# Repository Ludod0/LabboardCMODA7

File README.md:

# Cmod A7 — LabBoard V1

**A custom FPGA expansion PCB designed for the Digilent Cmod A7-35T.**

The **LabBoard V1** is a custom-designed PCB that expands the input/output capabilities of the Digilent Cmod A7 FPGA development board.

Designed using **KiCad**, the board provides LEDs, switches, a four-digit seven-segment display, and expansion connectors for experimenting with digital logic and VHDL development.

The project aims to provide a reusable hardware platform for FPGA experimentation, prototyping, and educational projects.

## Project Status

**Hardware prototype: Assembled and undergoing validation**

The PCB has been manufactured, assembled, and tested. Most peripherals are operational, including the four-digit display, DIP switches, and push buttons.

**Known issues:**
- All eight discrete LEDs are currently non-functional. Incorrect LED polarity during assembly is the suspected cause.
- Two expansion header signals have unconventional routing assignments that will be corrected in V2.

## Features

| Component | Quantity | Description |
|---|---|---|
| Discrete LEDs | 8 | GPIO-controlled LEDs |
| DIP switches | 4 | Digital inputs |
| Push buttons | 2 | Digital inputs; VHDL debouncing planned |
| Seven-segment display | 1 | Four multiplexed digits |
| Digital expansion headers | 2 | 8 signal connections each |
| Analog expansion header | 1 | 4-pin connector for analog signals |
| FPGA interface | 1 | Digilent Cmod A7-35T |

### Seven-Segment Display

The four-digit display is driven through a multiplexed architecture using external MOSFETs.

The FPGA controls the individual segment signals and selects the active digit through four common-anode control lines.

This arrangement allows the four digits to display different values through rapid time-division multiplexing.

### Digital Inputs

The LabBoard provides four DIP switches and two momentary push buttons for FPGA input.

A reusable VHDL debouncing module is planned for the push buttons.

## GPIO Pinout

The following table documents the **Cmod A7 physical PIO assignments** used by LabBoard V1.

| PIO | Signal | Description |
|---|---|---|
| 1 | `LED0` | Discrete LED 0 |
| 2 | `LED1` | Discrete LED 1 |
| 3 | `LED2` | Discrete LED 2 |
| 4 | `LED3` | Discrete LED 3 |
| 5 | `LED4` | Discrete LED 4 |
| 6 | `LED5` | Discrete LED 5 |
| 7 | `LED6` | Discrete LED 6 |
| 8 | `LED7` | Discrete LED 7 |
| 9 | `SEG_A` | Segment A |
| 10 | `SEG_B` | Segment B |
| 11 | `SEG_C` | Segment C |
| 12 | `SEG_D` | Segment D |
| 13 | `SEG_E` | Segment E |
| 14 | `SEG_F` | Segment F |
| 15 | `ANALOG_CON_1` | Analog input 1 |
| 16 | `ANALOG_CON_2` | Analog input 2 |
| 17 | `SEG_G` | Segment G |
| 18 | `SEG_DP` | Decimal point |
| 19 | `DIGI_1` | Digit 1 — common anode |
| 20 | `DIGI_2` | Digit 2 — common anode |
| 21 | `DIGI_3` | Digit 3 — common anode |
| 22 | `DIGI_4` | Digit 4 — common anode |
| 23 | `DIP_SW0` | DIP switch 0 |
| 24 | `VU` | USB voltage rail |
| 25 | `GND` | Ground |
| 26 | `DIP_SW1` | DIP switch 1 |
| 27 | `DIP_SW2` | DIP switch 2 |
| 28 | `DIP_SW3` | DIP switch 3 |
| 29 | `SP_0` | Push button 0 |
| 30 | `SP_1` | Push button 1 |
| 31 | `CON1_1` | Expansion connector 1 |
| 32 | `CON1_2` | Expansion connector 1 |
| 33 | `CON1_3` | Expansion connector 1 |
| 34 | `CON1_4` | Expansion connector 1 |
| 35 | `CON1_7` | Expansion connector 1 |
| 36 | `CON1_8` | Expansion connector 1 |
| 37 | `CON2_2` | Expansion connector 2 — V2 routing improvement planned |
| 38 | `CON1_10` | Expansion connector 1 |
| 39 | `CON2_1` | Expansion connector 2 |
| 40 | `CON1_9` | Expansion connector 1 — V2 routing improvement planned |
| 41 | `CON2_3` | Expansion connector 2 |
| 42 | `CON2_4` | Expansion connector 2 |
| 43 | `CON2_7` | Expansion connector 2 |
| 44 | `CON2_8` | Expansion connector 2 |
| 45 | `CON2_9` | Expansion connector 2 |
| 46 | `CON2_10` | Expansion connector 2 |
| 47 | `NC` | Not connected |
| 48 | `NC` | Not connected |

> **Note:** PIO 37 and PIO 40 are intentionally listed with their actual LabBoard V1 signal assignments. These are not documentation errors. Their routing will be improved in a future revision.

## Development Environment

- **PCB design:** KiCad
- **FPGA:** AMD/Xilinx Artix-7 (Cmod A7-35T)
- **Hardware description language:** VHDL
- **FPGA development:** AMD Vivado
- **Digital logic simulation:** Digital
- **Chip to use for Vivado projects:** xc7a35tcpg236-1
## Planned Improvements
- [ ] Develop and validate reusable VHDL input-debouncing modules.
- [ ] Improve expansion connector routing in LabBoard V2.
- [ ] Document hardware tests and add demonstration photographs.

## Project Purpose

This project is part of an ongoing effort to develop practical skills in FPGA design, PCB development, digital electronics, and hardware debugging.

The LabBoard is intended to serve as a reusable platform for future projects, including custom digital logic, counters, control systems, and experimental processor architectures.

---

**LabBoard V1 — Custom FPGA Hardware Development Project, 2026**

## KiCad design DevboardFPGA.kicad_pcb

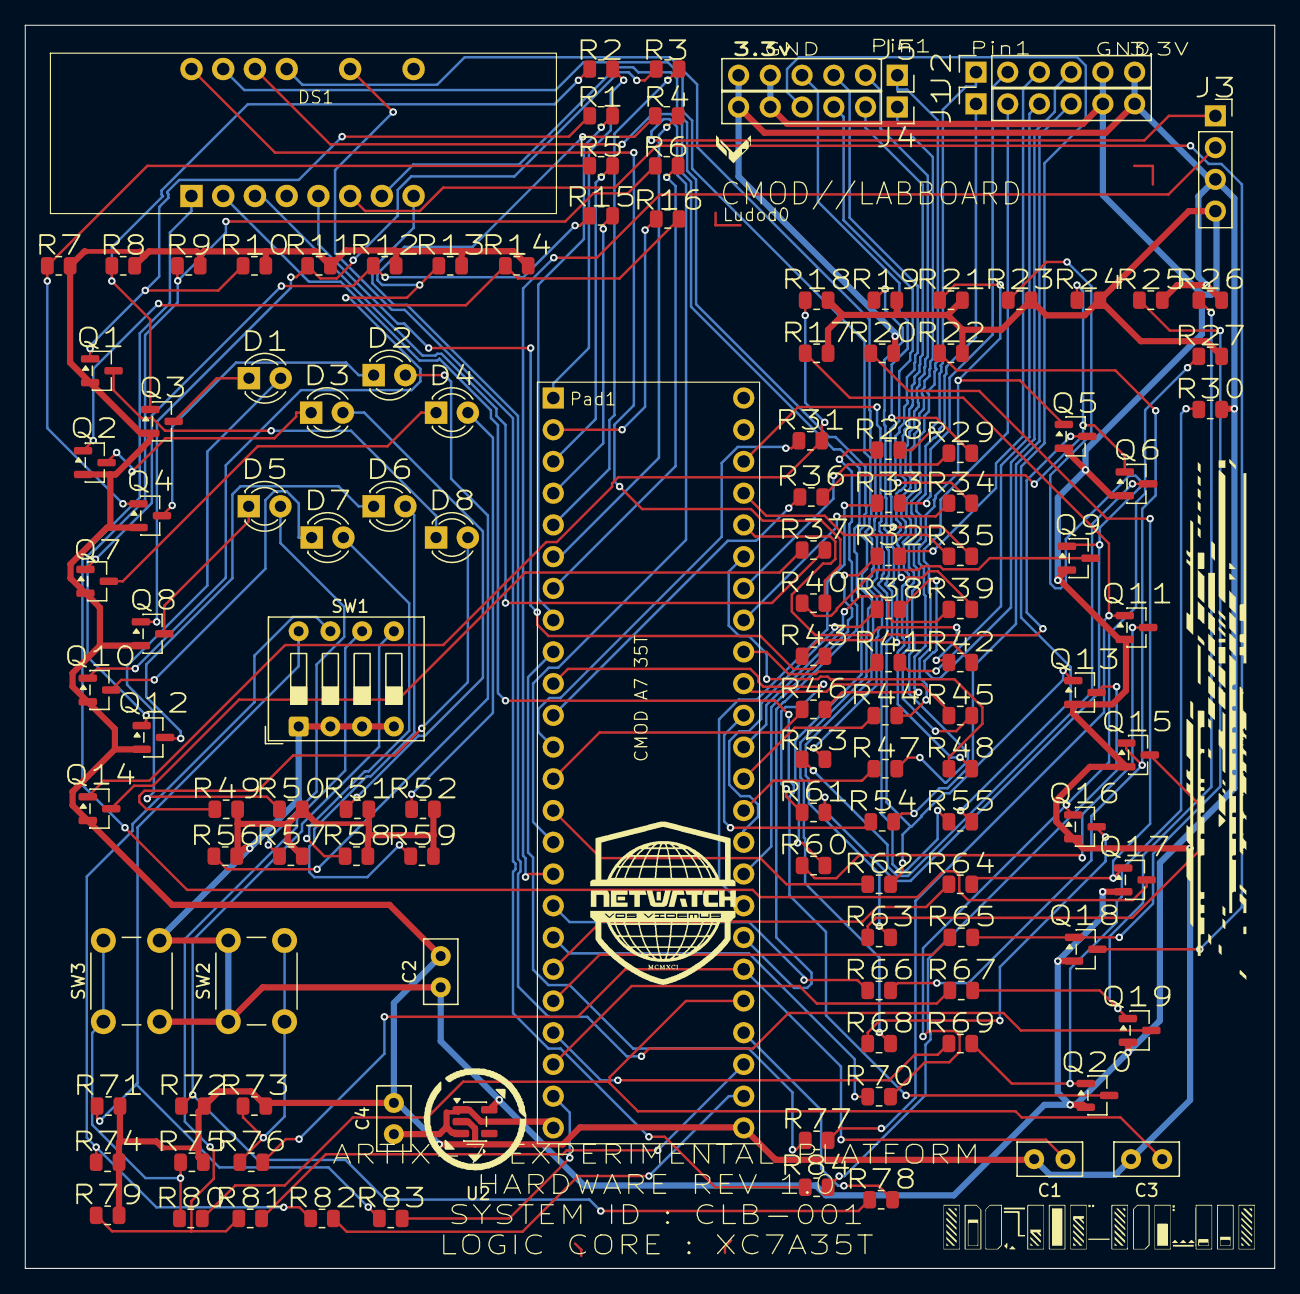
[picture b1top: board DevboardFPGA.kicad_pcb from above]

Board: 2 copper layers, 100.0 x 99.5 mm, 127 parts (0 on the bottom side), 125 nets.

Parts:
C1, C3: 100nF; C_Disc_D5.0mm_W2.5mm_P2.50mm
C2, C4: 2,2 uF; C_Disc_D5.0mm_W2.5mm_P2.50mm
D1, D2, D3, D4, D5, D6, D7, D8: LED; LED_D3.0mm
DS1: Untitled
J1, J2, J4, J5: Conn_01x06; PinSocket_1x06_P2.54mm_Vertical
J3: Conn_01x04; PinSocket_1x04_P2.54mm_Vertical
Q1, Q2, Q3, Q4, Q5, Q6, Q7, Q8, Q9, Q10, Q11, Q12, Q13, Q14, Q15, Q16: AO3400A; SOT-23
Q17, Q18, Q19, Q20: AO3401A; SOT-23
R1, R2, R3, R4, R5, R6, R15, R16, R31, R36, R37, R40, R43, R46, R53, R60, R61, R62, R63, R64, R65, R66, R67, R68, R69, R70, R77, R84: 330; R_0805_2012Metric
R7, R8, R9, R10, R11, R12, R13, R14, R17, R18, R19, R20, R21, R22, R23, R24, R25, R26, R27, R30: 100K; R_0805_2012Metric
R28, R29, R32, R33, R34, R35, R38, R39, R41, R42, R44, R45, R47, R48, R54, R55: 200; R_0805_2012Metric
R49, R50, R51, R52, R56, R57, R58, R59: 470; R_0805_2012Metric
R71, R72, R74, R79: 10K; R_0805_2012Metric
R73, R75: 10k; R_0805_2012Metric
R76, R78, R80, R81, R82, R83: 1k; R_0805_2012Metric
SW1: SW_DIP_x04; SW_DIP_SPSTx04_Slide_9.78x12.34mm_W7.62mm_P2.54mm
SW2, SW3: SW_Push; SW_PUSH_6mm
U1: CMOD_A7
U2: TLV75533PDBV; SOT-23-5

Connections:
+3.3V: C2.1, J1.6, J2.6, J3.3, J4.6, J5.6, Q17.2 (S), Q18.2 (S), Q19.2 (S), Q20.2 (S), R20.2, R25.2, R26.2, R30.2, R49.2, R50.2, R51.2, R52.2, R56.2, R57.2, R58.2, R59.2, SW1.1, SW1.2, SW1.3, SW1.4, SW2.1, SW3.1, U2.5 (OUT)
/5v to 3.3v/VU: C4.1, U1.24 (VU), U2.1 (IN), U2.3 (EN)
/ANALOGCON/ANALOG1: J3.1, U1.15 (AIN15)
/ANALOGCON/ANALOG2: J3.2, U1.16 (AIN16)
/EXTENSIONS/GPIO_PMOD01-1: R28.1, U1.31 (PIO31)
/EXTENSIONS/GPIO_PMOD01-2: R33.1, U1.32 (PIO32)
/EXTENSIONS/GPIO_PMOD01-3: R32.1, U1.33 (PIO33)
/EXTENSIONS/GPIO_PMOD01-4: R38.1, U1.34 (PIO34)
/EXTENSIONS/GPIO_PMOD01-7: R47.1, U1.35 (PIO35)
/EXTENSIONS/GPIO_PMOD01-8: R44.1, U1.36 (PIO36)
/EXTENSIONS/GPIO_PMOD01-9: R41.1, U1.40 (PIO40)
/EXTENSIONS/GPIO_PMOD01-10: R54.1, U1.38 (PIO38)
/EXTENSIONS/GPIO_PMOD02-1: R45.1, U1.39 (PIO39)
/EXTENSIONS/GPIO_PMOD02-2: R39.1, U1.37 (PIO37)
/EXTENSIONS/GPIO_PMOD02-3: R34.1, U1.41 (PIO41)
/EXTENSIONS/GPIO_PMOD02-4: R29.1, U1.42 (PIO42)
/EXTENSIONS/GPIO_PMOD02-7: R48.1, U1.43 (PIO43)
/EXTENSIONS/GPIO_PMOD02-8: R42.1, U1.44 (PIO44)
/EXTENSIONS/GPIO_PMOD02-9: R35.1, U1.45 (PIO45)
/EXTENSIONS/GPIO_PMOD02-10: R55.1, U1.46 (PIO46)
/HexIO/GPIO_DIGI_1: R64.1, U1.19 (PIO19)
/HexIO/GPIO_DIGI_2: R65.1, U1.20 (PIO20)
/HexIO/GPIO_DIGI_3: R69.1, U1.21 (PIO21)
/HexIO/GPIO_DIGI_4: R67.1, U1.22 (PIO22)
/HexIO/GPIO_SEG_A: R77.1, U1.9 (PIO9)
/HexIO/GPIO_SEG_B: R61.1, U1.10 (PIO10)
/HexIO/GPIO_SEG_C: R36.1, U1.11 (PIO11)
/HexIO/GPIO_SEG_D: R31.1, U1.12 (PIO12)
/HexIO/GPIO_SEG_DP: R70.1, U1.18 (PIO18)
/HexIO/GPIO_SEG_E: R46.1, U1.13 (PIO13)
/HexIO/GPIO_SEG_F: R62.1, U1.14 (PIO14)
/HexIO/GPIO_SEG_G: R66.1, U1.17 (PIO17)
/LED IO/GPIO_LED1: R2.1, U1.1 (PIO1)
/LED IO/GPIO_LED2: R16.1, U1.2 (PIO2)
/LED IO/GPIO_LED3: R5.1, U1.3 (PIO3)
/LED IO/GPIO_LED4: R15.1, U1.4 (PIO4)
/LED IO/GPIO_LED5: R3.1, U1.5 (PIO5)
/LED IO/GPIO_LED6: R4.1, U1.6 (PIO6)
/LED IO/GPIO_LED7: R6.1, U1.7 (PIO7)
/LED IO/GPIO_LED8: R1.1, U1.8 (PIO8)
/Switches/GPIO_SP0: C3.1, R80.2, U1.29 (PIO29)
/Switches/GPIO_SP1: C1.1, R76.2, U1.30 (PIO30)
/Switches/GPIO_SW0: R83.2, U1.23 (PIO23)
/Switches/GPIO_SW1: R82.2, U1.26 (PIO26)
/Switches/GPIO_SW2: R81.2, U1.27 (PIO27)
/Switches/GPIO_SW3: R78.2, U1.28 (PIO28)
GND: C1.2, C2.2, C3.2, C4.2, J1.5, J2.5, J3.4, J4.5, J5.5, Q1.2 (S), Q2.2 (S), Q3.2 (S), Q4.2 (S), Q5.2 (S), Q6.2 (S), Q7.2 (S), Q8.2 (S), Q9.2 (S), Q10.2 (S), Q11.2 (S), Q12.2 (S), Q13.2 (S), Q14.2 (S), Q15.2 (S), Q16.2 (S), R7.2, R8.2, R9.2, R10.2, R11.2, R12.2, R13.2, R14.2, R17.2, R18.2, R19.2, R21.2, R22.2, R23.2, R24.2, R27.2, R71.2, R72.2, R73.2, R74.2, R75.2, R79.2, U1.25 (GND), U2.2 (GND)
unnamed: D1.2 (A), R50.1
unnamed: D1.1 (K), Q3.3 (D)
unnamed: D2.2 (A), R56.1
unnamed: D2.1 (K), Q4.3 (D)
unnamed: D3.2 (A), R51.1
unnamed: D3.1 (K), Q2.3 (D)
unnamed: D4.2 (A), R52.1
unnamed: D4.1 (K), Q7.3 (D)
unnamed: D5.2 (A), R57.1
unnamed: D5.1 (K), Q8.3 (D)
unnamed: D6.2 (A), R59.1
unnamed: D6.1 (K), Q12.3 (D)
unnamed: D7.2 (A), R58.1
unnamed: D7.1 (K), Q10.3 (D)
unnamed: D8.2 (A), R49.1
unnamed: D8.1 (K), Q1.3 (D)
unnamed: DS1.1 (DIG1_CA), Q17.3 (D)
unnamed: DS1.2 (DIG2_CA), Q20.3 (D)
unnamed: DS1.6 (DIG3_CA), Q18.3 (D)
unnamed: DS1.8 (DIG4_CA), Q19.3 (D)
unnamed: DS1.16 (SEG_B), R40.2
unnamed: DS1.13 (SEG_C), R53.2
unnamed: DS1.3 (SEG_D), R37.2
unnamed: DS1.7 (SEG_DP), R68.2
unnamed: DS1.5 (SEG_E), R43.2
unnamed: DS1.11 (SEG_F), R84.2
unnamed: DS1.15 (SEG_G), R63.2
unnamed: DS1.14 (Seg_A), R60.2
unnamed: J1.1, R47.2
unnamed: J1.2, R44.2
unnamed: J1.3, R41.2
unnamed: J1.4, R54.2
unnamed: J2.1, R28.2
unnamed: J2.2, R33.2
unnamed: J2.3, R32.2
unnamed: J2.4, R38.2
unnamed: J4.1, R48.2
unnamed: J4.2, R42.2
unnamed: J4.3, R35.2
unnamed: J4.4, R55.2
unnamed: J5.1, R45.2
unnamed: J5.2, R39.2
unnamed: J5.3, R34.2
unnamed: J5.4, R29.2
unnamed: Q1.1 (G), R1.2, R10.1
unnamed: Q2.1 (G), R14.1, R16.2
unnamed: Q3.1 (G), R2.2, R8.1
unnamed: Q4.1 (G), R5.2, R7.1
unnamed: Q5.3 (D), R43.1
unnamed: Q5.1 (G), R21.1, R46.2
unnamed: Q6.3 (D), R53.1
unnamed: Q6.1 (G), R24.1, R36.2
unnamed: Q7.1 (G), R12.1, R15.2
unnamed: Q8.1 (G), R3.2, R11.1
unnamed: Q9.3 (D), R40.1
unnamed: Q9.1 (G), R23.1, R61.2
unnamed: Q10.1 (G), R4.2, R13.1
unnamed: Q11.3 (D), R60.1
unnamed: Q11.1 (G), R17.1, R77.2
unnamed: Q12.1 (G), R6.2, R9.1
unnamed: Q13.3 (D), R84.1
unnamed: Q13.1 (G), R19.1, R62.2
unnamed: Q14.3 (D), R37.1
unnamed: Q14.1 (G), R18.1, R31.2
unnamed: Q15.3 (D), R63.1
unnamed: Q15.1 (G), R22.1, R66.2
unnamed: Q16.3 (D), R68.1
unnamed: Q16.1 (G), R27.1, R70.2
unnamed: Q17.1 (G), R20.1, R64.2
unnamed: Q18.1 (G), R25.1, R65.2
unnamed: Q19.1 (G), R26.1, R67.2
unnamed: Q20.1 (G), R30.1, R69.2
unnamed: R71.1, R83.1, SW1.8
unnamed: R72.1, R78.1, SW1.5
unnamed: R73.1, R76.1, SW2.2
unnamed: R74.1, R82.1, SW1.7
unnamed: R75.1, R80.1, SW3.2
unnamed: R79.1, R81.1, SW1.6
